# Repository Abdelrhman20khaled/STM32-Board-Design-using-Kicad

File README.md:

# STM32 Board Design using KiCad

## Overview

This repository showcases the design of a **custom STM32F100CTB development board**, created using **KiCad** as part of a **Learning & Development (L&D)**.
The board serves as a hands-on platform for exploring **embedded systems**, **ARM Cortex-M microcontrollers**, and **mixed-signal PCB design** practices.

The goal of this project is to provide a compact yet powerful **training and development board** that allows learners to understand the fundamentals of microcontroller hardware, PCB layout, and circuit design — from schematic to prototype.

> The image above shows the top and bottom view of the PCB — featuring the STM32 microcontroller at the center, USB Type-B port at the top, and dual GPIO headers for flexible use.

---

## Key Features

- **Microcontroller**
  - STM32F100 (ARM Cortex-M3) — ideal for entry-level embedded learning and control applications  
  - QFP package for reliable assembly and accessible signal routing  

- **Connectivity & Expansion**
  - Dual header rows (J5, J6) providing access to all GPIO pins  
  - USB Type-B connector for power and programming  
  - SWD header for debugging and firmware upload  

- **User Controls**
  - Tactile pushbutton (SW1) for reset or user input  
  - Slide switch (SW2) for mode selection or power control  

- **Power Management**
  - On-board regulation from 5V or USB to 3.3V  
  - Decoupling capacitors and ferrite filtering for clean power delivery  
  - Supports both USB and external supply input  

- **PCB Design**
  - Designed entirely in **KiCad**  
  - **4-layer stack-up** for signal and power integrity  
  - Inner layers dedicated to **power and ground planes**  
  - Careful analog/digital separation for reduced noise and EMI  
  - Compact form factor with clean routing and labeled headers  

---

## Design Goals

This board was developed with the following objectives:

- Serve as a **training and educational tool** for PCB design and embedded systems.  
- Provide a **reusable development board** for experimenting with STM32 peripherals (GPIO, UART, SPI, I²C, ADC, PWM, etc.).  
- Explore **best practices in mixed-signal layout**, decoupling, and grounding.  
- Strengthen understanding of **KiCad workflow**, from schematic capture to PCB fabrication and assembly.  

### Key Components

| Reference | Component | Function |
|------------|------------|----------|
| U1 | STM32F100CTB | Main microcontroller |
| U2 | Voltage regulator | 5V → 3.3V conversion |
| Y2 | Crystal oscillator | MCU clock source |
| SW1 | Pushbutton | Reset/User input |
| SW2 | Slide switch | Mode/Power select |
| J5 / J6 | Pin headers | GPIO expansion |
| J4 | SWD header | Debug/programming interface |
| USB | Type-B connector | Power & communication |

---

## Learning Outcomes

Through this project, students and engineers gain hands-on experience with:

- **Schematic design** in KiCad  
- **Component library management**   
- **Grounding and decoupling strategies**  

This board also provides a reusable reference for future mixed-signal designs and embedded control experiments.

---

## Applications

- Embedded systems education and prototyping  
- Real-time control and automation projects  
- Peripheral testing and firmware development  
- Hardware design learning modules  

---

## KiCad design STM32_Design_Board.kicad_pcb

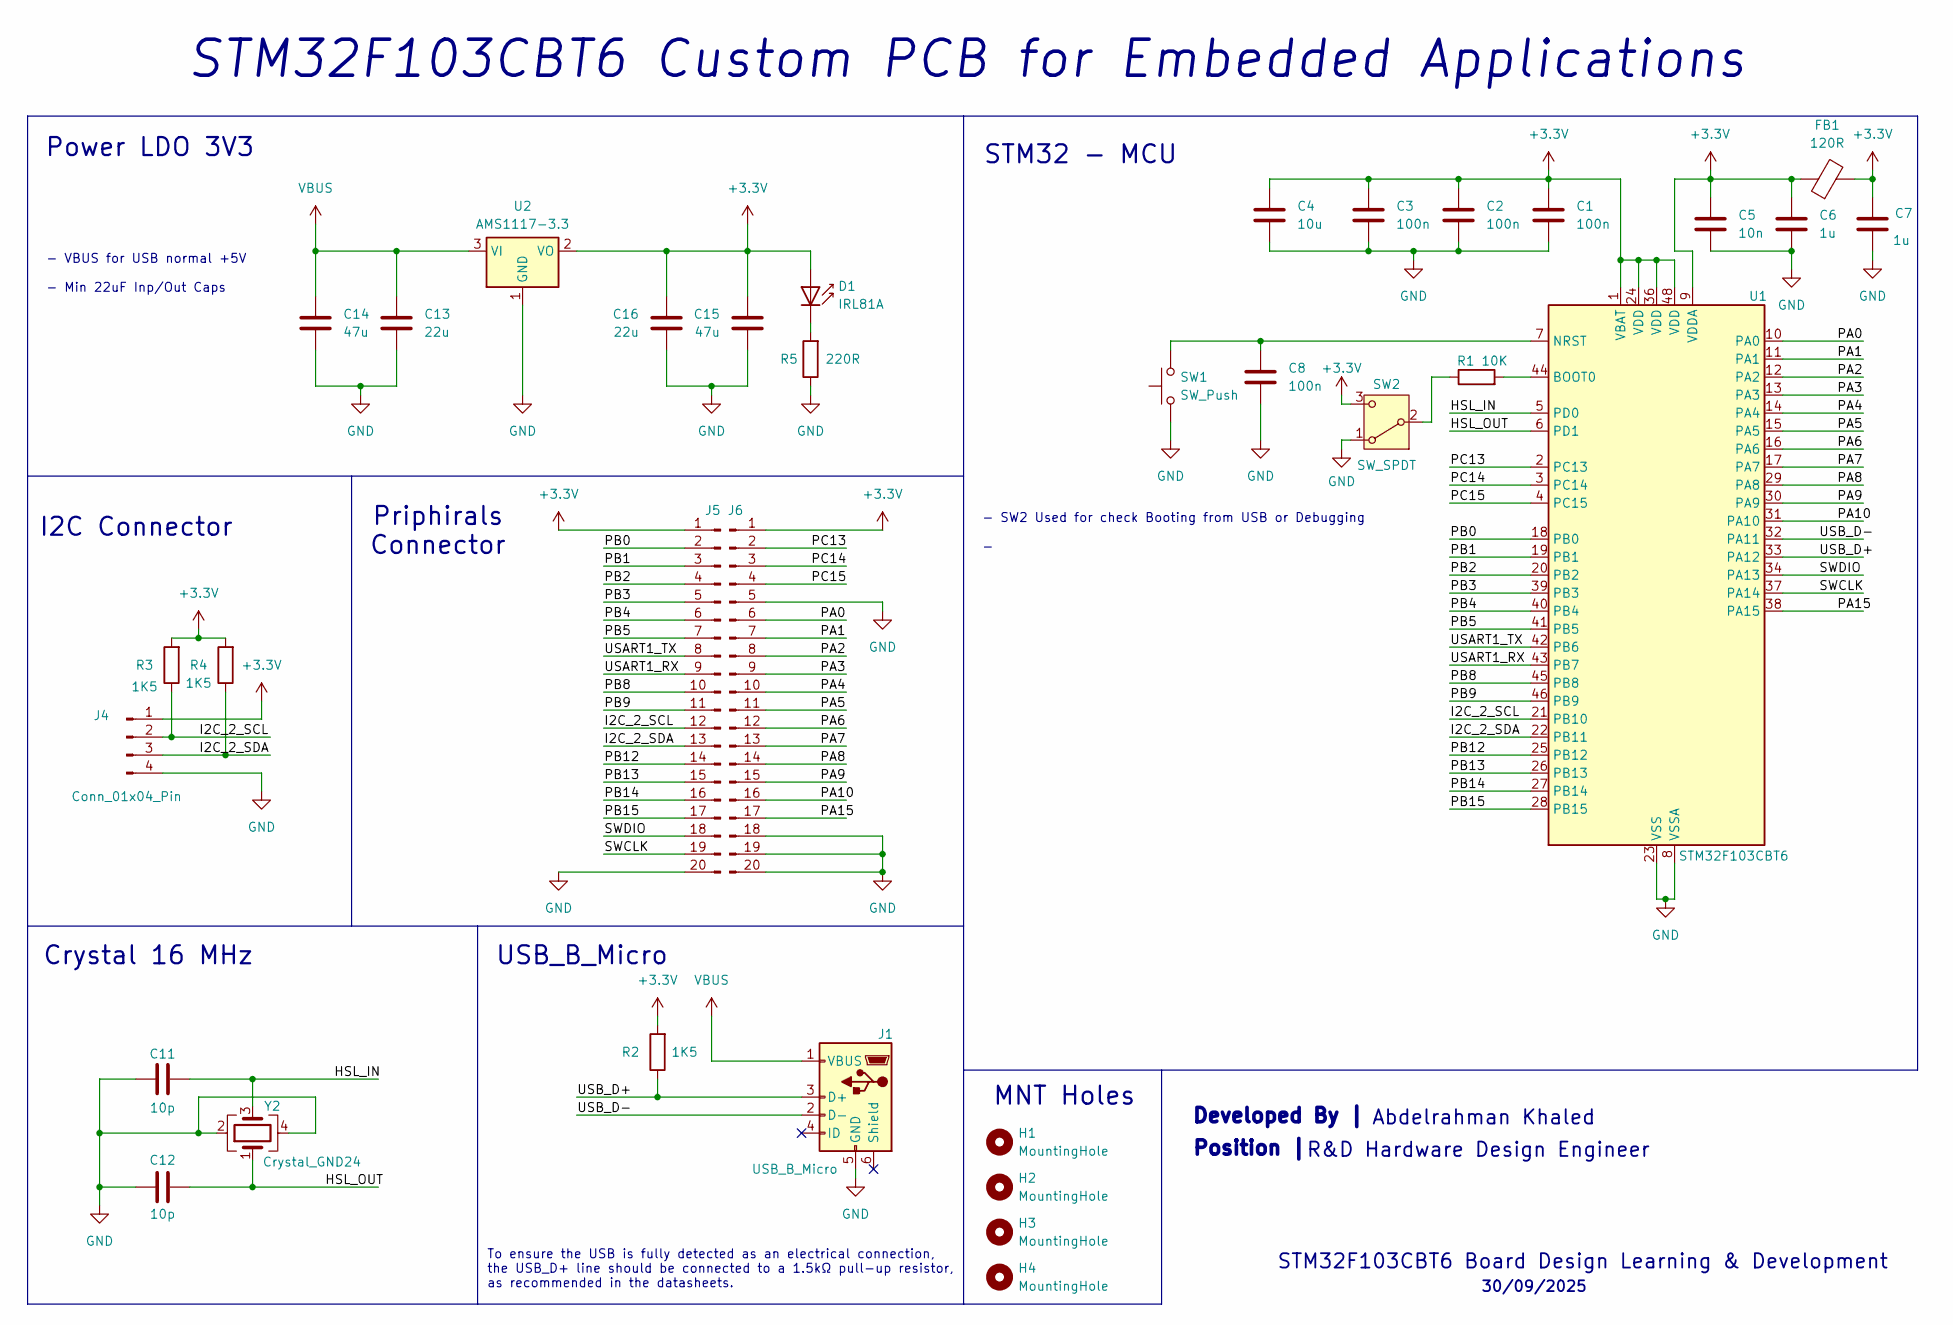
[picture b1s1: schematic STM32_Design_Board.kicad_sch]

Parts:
C1, C2, C3, C8: 100n; C_0805_2012Metric
C4: 10u; C_0805_2012Metric
C5: 10n; C_0805_2012Metric
C6, C7: 1u; C_0805_2012Metric
C11, C12: 10p; C_0805_2012Metric
C13, C16: 22u; C_0805_2012Metric
C14, C15: 47u; C_0805_2012Metric
D1: IRL81A; D_0805_2012Metric
FB1: 120R; R_2010_5025Metric
H1, H2, H3, H4: MountingHole; MountingHole_2.2mm_M2_ISO14580
J1: USB_B_Micro; USB_Micro-B_Wuerth_629105150521
J4: Conn_01x04_Pin; PinHeader_1x04_P2.54mm_Vertical
J5, J6: Conn_01x20_Pin; PinHeader_1x20_P2.54mm_Vertical
R1: 10K; R_0805_2012Metric
R2, R3, R4: 1K5; R_0805_2012Metric
R5: 220R; R_0805_2012Metric
SW1: SW_Push; SW_PUSH_6mm_H4.3mm
SW2: SW_SPDT; SW_SPDT_PCM12
U1: STM32F103CBT6; LQFP-48_7x7mm_P0.5mm
U2: AMS1117-3.3; SOT-223-3_TabPin2
Y2: Crystal_GND24; Crystal_SMD_SeikoEpson_FA238V-4Pin_3.2x2.5mm

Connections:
+3.3V: C1.1, C2.1, C3.1, C4.1, C5.1, C6.1, C7.1, C15.1, C16.1, D1.2 (A), FB1.1, FB1.2, J4.1, J5.1, J6.1, R2.2, R3.2, R4.2, SW2.3 (C), U1.1 (VBAT), U1.9 (VDDA), U1.24 (VDD), U1.36 (VDD), U1.48 (VDD), U2.2 (VO)
/HSL_IN: C11.2, U1.5 (PD0), Y2.3
/HSL_OUT: C12.2, U1.6 (PD1), Y2.1
/I2C_2_SCL: J4.2, J5.12, R3.1, U1.21 (PB10)
/I2C_2_SDA: J4.3, J5.13, R4.1, U1.22 (PB11)
/PA0: J6.6, U1.10 (PA0)
/PA1: J6.7, U1.11 (PA1)
/PA2: J6.8, U1.12 (PA2)
/PA3: J6.9, U1.13 (PA3)
/PA4: J6.10, U1.14 (PA4)
/PA5: J6.11, U1.15 (PA5)
/PA6: J6.12, U1.16 (PA6)
/PA7: J6.13, U1.17 (PA7)
/PA8: J6.14, U1.29 (PA8)
/PA9: J6.15, U1.30 (PA9)
/PA10: J6.16, U1.31 (PA10)
/PA15: J6.17, U1.38 (PA15)
/PB0: J5.2, U1.18 (PB0)
/PB1: J5.3, U1.19 (PB1)
/PB2: J5.4, U1.20 (PB2)
/PB3: J5.5, U1.39 (PB3)
/PB4: J5.6, U1.40 (PB4)
/PB5: J5.7, U1.41 (PB5)
/PB8: J5.10, U1.45 (PB8)
/PB9: J5.11, U1.46 (PB9)
/PB12: J5.14, U1.25 (PB12)
/PB13: J5.15, U1.26 (PB13)
/PB14: J5.16, U1.27 (PB14)
/PB15: J5.17, U1.28 (PB15)
/PC13: J6.2, U1.2 (PC13)
/PC14: J6.3, U1.3 (PC14)
/PC15: J6.4, U1.4 (PC15)
/SWCLK: J5.19, U1.37 (PA14)
/SWDIO: J5.18, U1.34 (PA13)
/USART1_RX: J5.9, U1.43 (PB7)
/USART1_TX: J5.8, U1.42 (PB6)
/USB_D+: J1.3 (D+), R2.1, U1.33 (PA12)
/USB_D-: J1.2 (D-), U1.32 (PA11)
GND: C1.2, C2.2, C3.2, C4.2, C5.2, C6.2, C7.2, C8.2, C11.1, C12.1, C13.2, C14.2, C15.2, C16.2, J1.5 (GND), J4.4, J5.20, J6.5, J6.18, J6.19, J6.20, R5.1, SW1.1, SW2.1 (A), U1.8 (VSSA), U1.23 (VSS), U1.35 (VSS), U1.47 (VSS), U2.1 (GND), Y2.2, Y2.4
unnamed: D1.1 (K), R5.2
unnamed: R1.1, SW2.2 (B)
unnamed: R1.2, U1.44 (BOOT0)
unnamed: C8.1, SW1.2, U1.7 (NRST)
VBUS: C13.1, C14.1, J1.1 (VBUS), U2.3 (VI)

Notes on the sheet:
USB_B_Micro
- SW2 Used for check Booting from USB or Debugging -
Abdelrahman Khaled
To ensure the USB is fully detected as an electrical connection, the USB_D+ line should be connected to a 1.5kΩ pull-up resistor, as recommended in the datasheets.
STM32F103CBT6 Board Design Learning & Development
MNT Holes
STM32 - MCU
STM32F103CBT6 Custom PCB for Embedded Applications
I2C Connector
- VBUS for USB normal +5V - Min 22uF Inp/Out Caps
Priphirals Connector
Crystal 16 MHz
R&D Hardware Design Engineer
Developed By |
Position |
Power LDO 3V3
30/09/2025

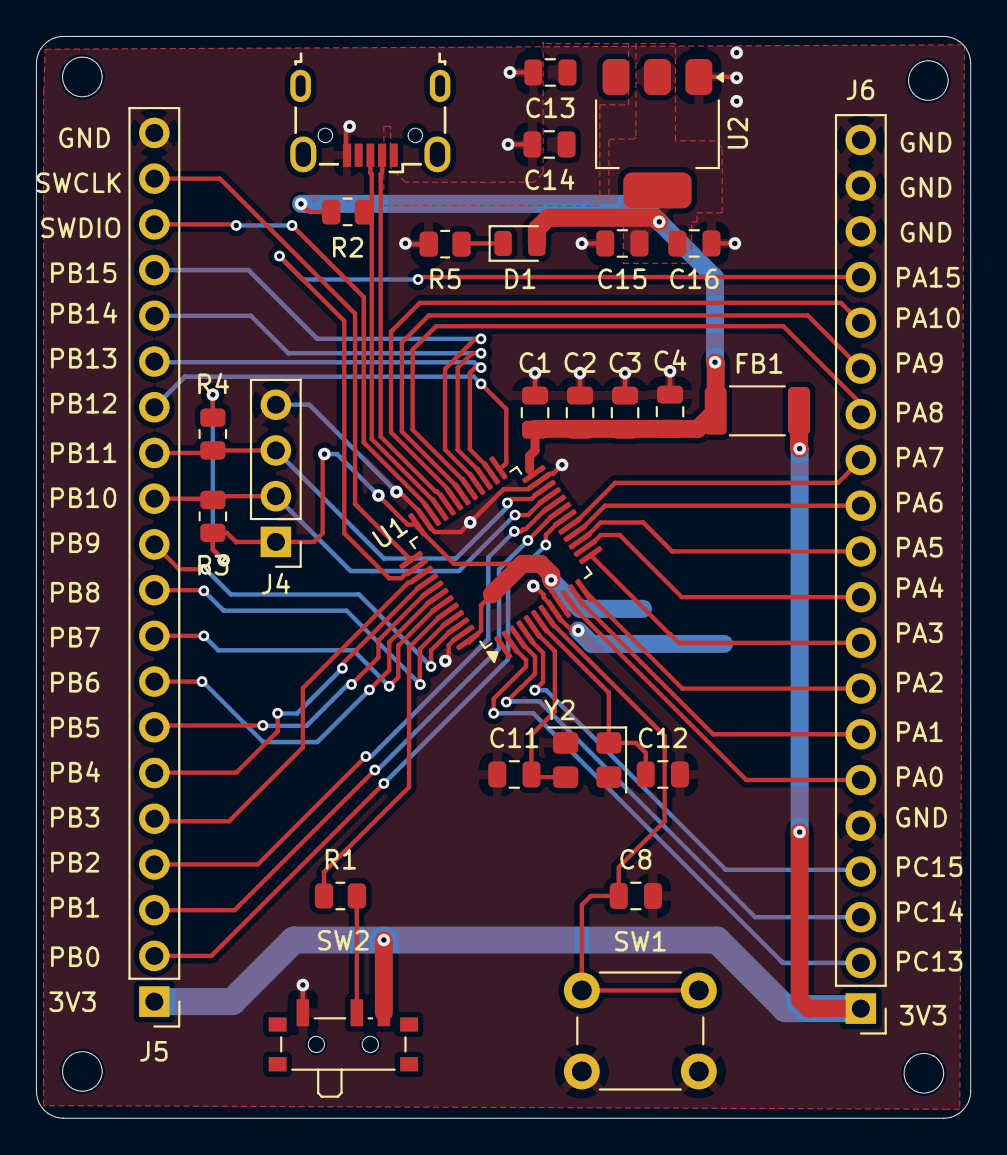
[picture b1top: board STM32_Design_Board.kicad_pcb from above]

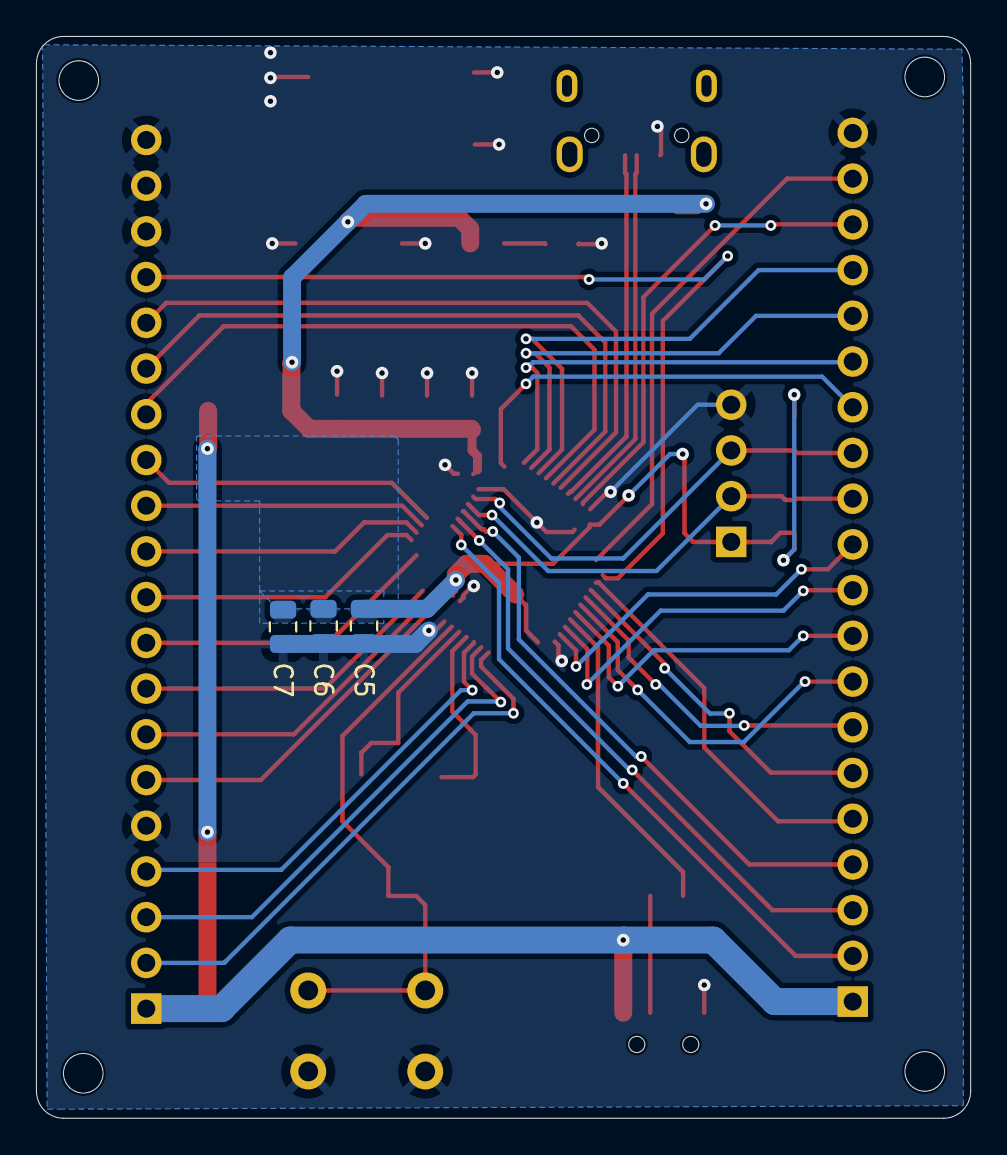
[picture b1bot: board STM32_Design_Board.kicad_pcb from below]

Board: 2 copper layers, 51.9 x 60.1 mm, 34 parts (3 on the bottom side), 44 nets.
